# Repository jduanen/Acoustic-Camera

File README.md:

# Acoustic Camera — Project Summary

This project involves the design and implementation of a low-cost,
high-performance acoustic camera: i.e., a microphone array computes a power map
of the sound sources in a video camera's field of view and overlays it on the
video in real time.

Uses of such a device include locating vibration, gas leaks and electrical
breakdown, and as a hearing aid for people who can no longer localize sound
with one functional ear.

One of the top-level objectives for this project is to explore the use of
deep-learning models for this application and compare the performance and cost
with that of traditional DSP-based beamforming algorithms.

A full technical overview of the project can be found in [OVERVIEW.md](./OVERVIEW.md);
see the linked documents for more detail.

The Phase 3 prototype (4x4-mic array) unit looks like this:
<br>

This is an animation of the current state of the Phase 4 (96-mic spiral array) version's PCBs: 

See an example of a commercial product here [Fluke](https://youtu.be/UPVcwDzhBZ8) and a low-cost consumer product here [Fotric](https://youtu.be/MBhJoPzHv2Y)

## How it works

The microphone array samples the sound field at every mic at once. For each candidate direction
(azimuth, elevation), a **steering vector** describes the expected phase pattern across the
mics; a **beamformer** scores each direction against the measured **cross-spectral matrix
(CSM)** and the scores form the energy map overlaid on the video.

Three array properties set performance:

| Property | Controls | Rule |
|---|---|---|
| Aperture *D* | Beam width (resolution) and low-frequency limit | HPBW ≈ 58° × λ/*D*; useful directionality needs *f* > *c*/*D* |
| Minimum mic spacing *d* | High-frequency limit (grating lobes above it) | *f*<sub>Nyq</sub> = *c* / (2*d*) |
| Mic layout and count | Sidelobe level (MSL), SNR | Irregular spacing suppresses aliasing; more mics lower sidelobes |

Other key ideas: far field begins at *r* > 2*D*²/λ; the **point spread function** is how the
array smears a point source; commercial cameras average power incoherently across an octave
band to cut noise. Details: [BACKGROUND.md](./BACKGROUND.md), [MIC_ARRAYS.md](./MIC_ARRAYS.md).

**Algorithms explored** (one per family): Delay-and-Sum (simple, robust, wide beam), MVDR
(adaptive, suppresses interferers), CLEAN-SC (deconvolution, removes PSF artifacts), MUSIC
(subspace, super-resolution when the source count is known). ML methods come in Phase 5.

## Requirements and key design choices

| Parameter | Target |
|---|---|
| Frequency range | 200 Hz: 8 kHz (useful imaging from ~2 kHz) |
| Resolution (HPBW) | ~9.4° @ 8 kHz, ~19° @ 4 kHz, ~82° @ 1 kHz (simulated, Phase 4 array) |
| Distance | ~0.5 m (far-field limit) to ~10 m |
| Field of view | ±45° H, ±30° V, matched to the camera |
| Array | ~300 mm aperture, 96 MEMS mics, Underbrink 12 × 8 log-spiral, 12.94 mm min spacing (Nyquist ≈ 13.3 kHz) |

Why these numbers ([TRADEOFFS.md](./TRADEOFFS.md)):
- **300 mm aperture** is the practical sweet spot: portable, yet ~9° at 8 kHz. 5° at 1 kHz
  would need a ~4 m aperture.
- **96 mics** matches commercial practice (gfai Mikado uses 96 in the same pattern). Mic count
  grows as (aperture/spacing)², so going much smaller in spacing costs ~400+ mics.
- **Underbrink spiral** gave the best sidelobe suppression of all patterns simulated
  (−24.4 dB @ 4 kHz), with circular symmetry.
- **Beamforming grid**: 2–3 points per HPBW is enough. Finer grids cost memory and time
  (the steering matrix dominates) without improving resolution; the 96-mic array needs a
  finer grid than the UMA-16's 0.5°–1°.

## Development phases

Each phase delivers a working end-to-end system ([PLAN.md](./PLAN.md)).

| Phase | Hardware | Goal | Status |
|---|---|---|---|
| 1 | Simulation | Validate algorithms and array geometry | Complete |
| 2 | ReSpeaker XVF3800 (4 mics, 90 mm) | First end-to-end pipeline: capture → beamform → overlay | Complete |
| 3 | miniDSP UMA-16 v2 (16 mics, 126 mm) | 2D (az × el) beamforming, calibration, touch UI | Complete |
| 4 | Custom PCBs (96 mics, 300 mm, FPGA) | Full-performance system | In progress |
| 5 | Phase 3/4 hardware | ML beamformer (PILOT / CRNN) vs CLEAN-SC | Not started |

### Phase 1 — simulation ([PHASE1.md](./PHASE1.md))
- Recommended array: Underbrink 12 × 8, α = 22°, 96 mics, 300 mm, 12.9 mm minimum spacing, alias-free to ~13 kHz.
- HPBW: >180° below 500 Hz, ~82° @ 1 kHz, ~37° @ 2 kHz, ~19° @ 4 kHz, ~9° @ 8 kHz.
- Algorithm choice: CLEAN-SC for real-time single-source display; MVDR for multiple or weak
  sources; MUSIC for closely spaced sources with known count; D&S for lowest latency.
  256 snapshots per CSM.
- Works well: industrial source hunting at 2–8 kHz, multi-source scenes, normal rooms,
  near field at 0.5–3 m. Not suited: below 1 kHz, very reverberant spaces (DRR < 3 dB),
  separating sources on the same bearing, MUSIC at SNR < 10 dB.

### Phase 2 — ReSpeaker smoke test ([PHASE2.md](./PHASE2.md))
- Raw mics are USB channels 2–5; gain imbalance up to ~3.6× motivated calibration.
- D&S, MVDR and CLEAN-SC agreed within 5°. Live script: `src/acoustic_camera_p2.py`.

### Phase 3 — UMA-16 ([PHASE3.md](./PHASE3.md))
- 16 channels at 48 kHz, 2D beamforming with full-frame overlay on webcam or Pi camera.
- Live script `src/acoustic_camera_p3.py` with a touch UI: frequency sliders and spectrum
  pan, energy threshold (auto/manual), zoom/recenter/dwell, power indicator, saved settings.
- Shared math in `src/beamforming.py` (pytest suite in `tests/`); `src/benchmark_algos.py`
  measures per-algorithm cost. A 1°/pt grid brings all four algorithms within 20 fps.
- Lesson: the UMA-16's usable window is only ~2–4 kHz, bounded by aperture below and
  spatial Nyquist above.

### Phase 4 — custom hardware ([PHASE4.md](./PHASE4.md))
96-mic Underbrink spiral, 12 arms × 8 mics, with PDM → CIC/FIR decimation in an FPGA and
data streamed to a host (96 ch × 48 kHz × 24 bit ≈ 110 Mbit/s, within 1 GbE). A Pi Camera
Module 3 Wide mounts through the centre of the array.

- **Single-FPGA design (primary).** One ALINX AC7200 module (Xilinx XC7A200T) runs all 96
  channels plus a GbE/UDP link. RTL is done and fits (43.5% LUTs for the pipeline, 48.1% with
  the GbE MAC and packetizer). Two boards:
  - `mic_array`: Ø320 mm, 96 Infineon IM72D128 mics, TCXO and clock tree, local 3.3 V LDOs.
  - `front_end`: AC7200 module, power regulation, DP83867 GbE PHY.
  - Joined by Panasonic P5KS board-to-board connectors (9 mm mated height).
  - Status: the current Phase 4 design; PCBs being laid out and prepared for fabrication. See
    [pcb/SCHEMATIC_NOTES.md](./pcb/SCHEMATIC_NOTES.md) for the current schematic, power and
    connector details.
- **Multi-FPGA alternate.** Four Cmod A7-35T cluster boards (24 mics each) feed a hub board
  over a shared-clock spoke bus; the hub relays to a Raspberry Pi 5 over USB. Breadboarded
  and laid out as PCBs, but the boards were never built.

### Phase 5 — ML
Needs real Phase 3/4 data to train and validate models.

## Landscape

- **Commercial products** ([PRODUCTS.md](./PRODUCTS.md)): 64–96 MEMS mics is the sweet spot
  for handheld far-field use; USB for portable, PoE for fixed installs; a co-located video
  camera at the array centre is universal.
- **Open-source projects** ([PROJECTS.md](./PROJECTS.md)): FPGA → GbE → GPU host is the
  established pattern above ~96 mics; cross-correlation calibration with GPU gradient descent
  (Ben Wang) recovers mic positions and speed of sound. This project uses **Acoular** (Python)
  for parts of its beamforming work.

## Open questions and TODOs

- Match camera optics to the array's FOV and resolution
- Partition processing between FPGA and host; choose final processing/display hardware
- Packaging; low-noise audio front-end layout
- Add-on arms to extend the aperture for better low-frequency resolution

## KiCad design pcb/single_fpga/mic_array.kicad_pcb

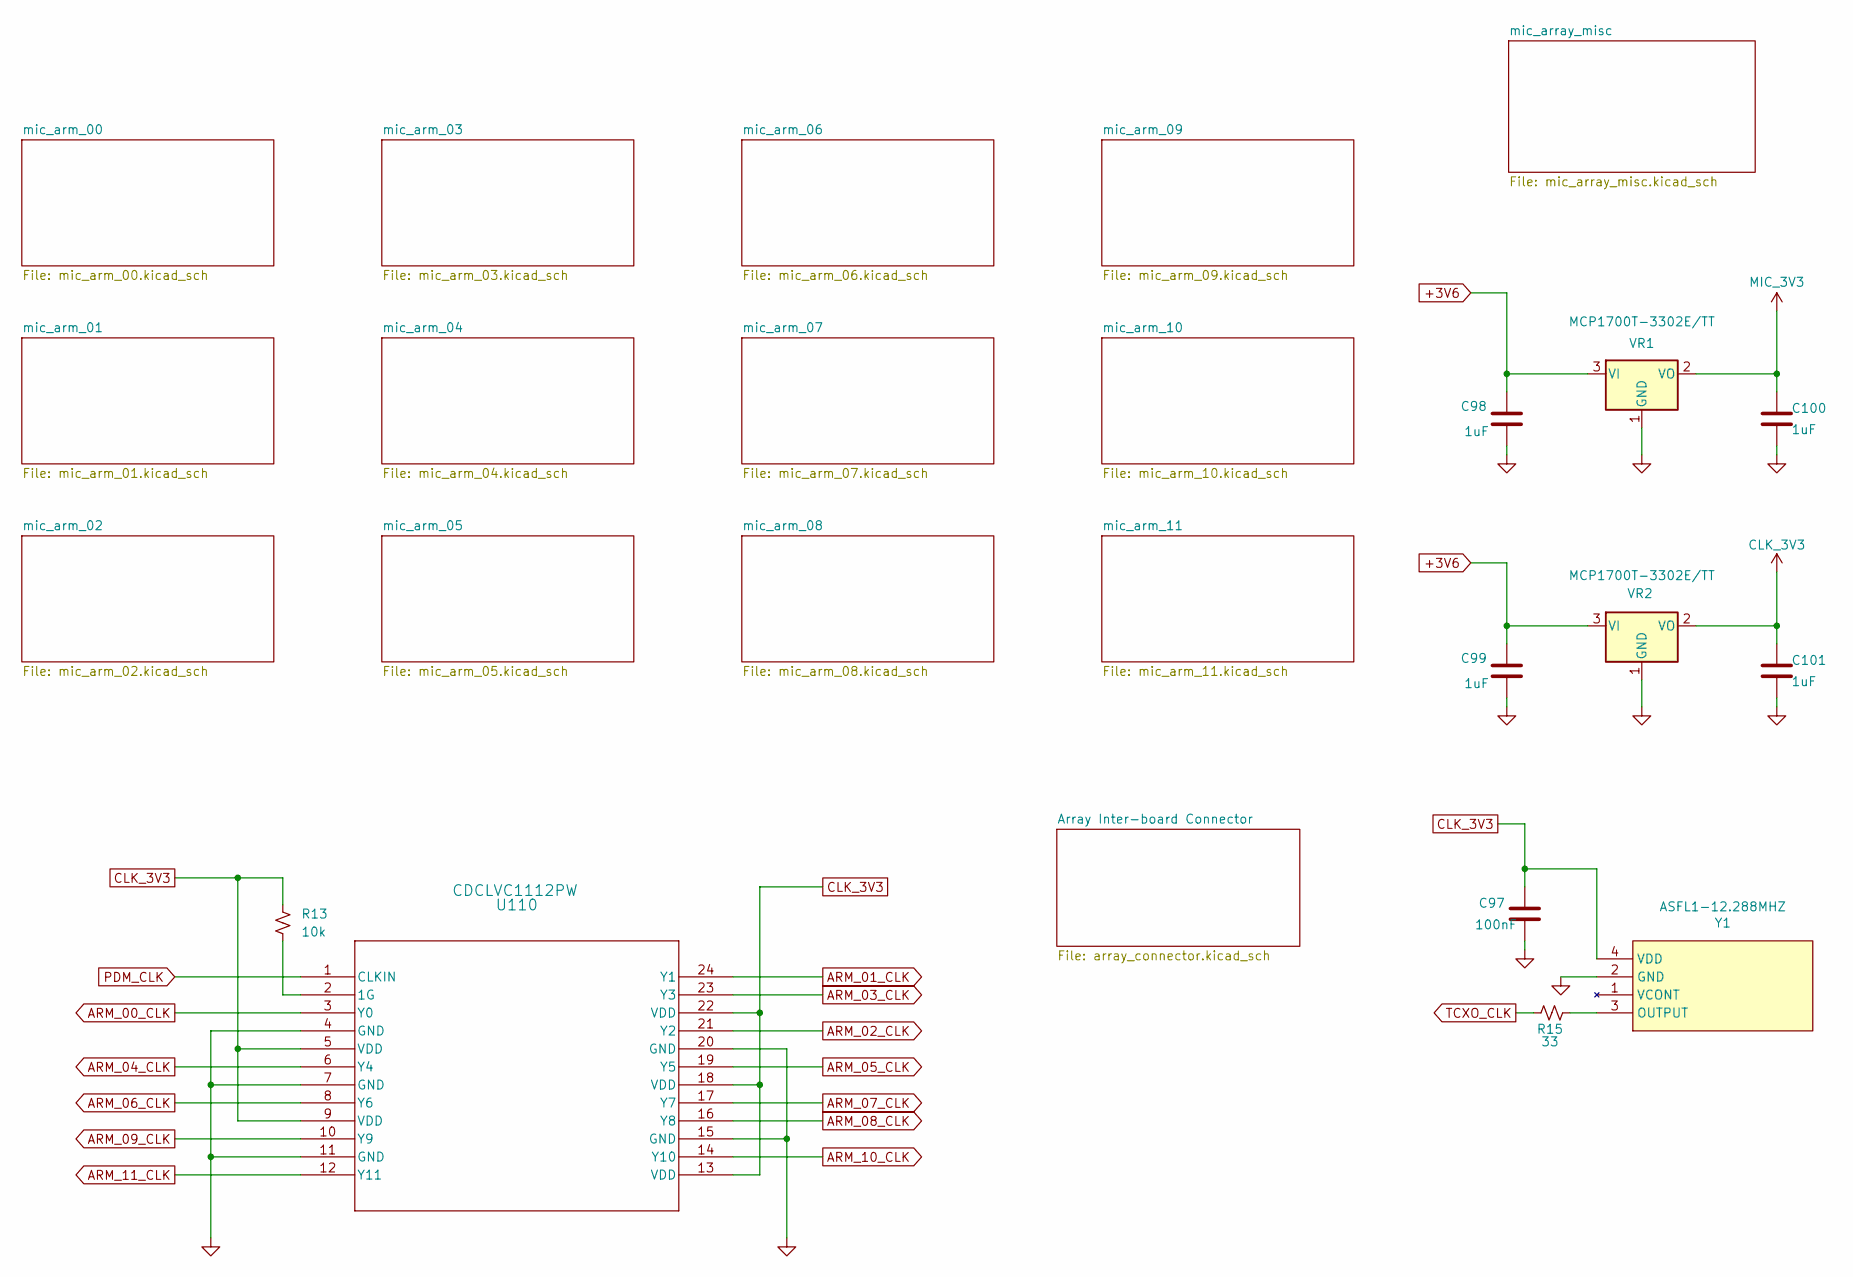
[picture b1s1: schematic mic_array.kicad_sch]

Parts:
C97: 100nF; C_0603_1608Metric; Part Number CC0603KRX7R9BB104; LCSC Part # C14663
C98, C99, C100, C101: 1uF; C_1206_3216Metric; Part Number CL31B105KBHNNNE; LCSC Part # C1848
R13: 10k; R_0603_1608Metric; Part Number 0603WAF1002T5E; LCSC Part # C25804
R15: 33; R_0603_1608Metric; Part Number 0603WAF330JT5E; LCSC Part # C23140
U110: CDCLVC1112PW; PW24; Part Number CDCLVC1112PWR; LCSC Part # C2876940
VR1, VR2: MCP1700T-3302E/TT; SOT-23; Part Number MCP1700T-3302E/TT; LCSC Part # C39051
Y1: ASFL1-12.288MHZ; Oscillator_SMD_SeikoEpson_SG8002LB-4Pin_5.0x3.2mm; Part Number ASFL1-12.288MHZ-LCS-T; LCSC Part # C276419

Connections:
+3V6: C98.1, C99.1, VR1.3 (VI), VR2.3 (VI); also elsewhere on the board
ARM_00_CLK: U110.3 (Y0); also elsewhere on the board
ARM_01_CLK: U110.24 (Y1); also elsewhere on the board
ARM_02_CLK: U110.21 (Y2); also elsewhere on the board
ARM_03_CLK: U110.23 (Y3); also elsewhere on the board
ARM_04_CLK: U110.6 (Y4); also elsewhere on the board
ARM_05_CLK: U110.19 (Y5); also elsewhere on the board
ARM_06_CLK: U110.8 (Y6); also elsewhere on the board
ARM_07_CLK: U110.17 (Y7); also elsewhere on the board
ARM_08_CLK: U110.16 (Y8); also elsewhere on the board
ARM_09_CLK: U110.10 (Y9); also elsewhere on the board
ARM_10_CLK: U110.14 (Y10); also elsewhere on the board
ARM_11_CLK: U110.12 (Y11); also elsewhere on the board
CLK_3V3: C97.1, C101.1, R13.2, U110.5 (VDD), U110.9 (VDD), U110.13 (VDD), U110.18 (VDD), U110.22 (VDD), VR2.2 (VO), Y1.4 (VDD); also elsewhere on the board
GND: C97.2, C98.2, C99.2, C100.2, C101.2, U110.4 (GND), U110.7 (GND), U110.11 (GND), U110.15 (GND), U110.20 (GND), VR1.1 (GND), VR2.1 (GND), Y1.2 (GND); also elsewhere on the board
MIC_3V3: C100.1, VR1.2 (VO); also elsewhere on the board
unnamed: R13.1, U110.2 (1G)
unnamed: R15.2, Y1.3 (OUTPUT)
PDM_CLK: U110.1 (CLKIN); also elsewhere on the board
TCXO_CLK: R15.1; also elsewhere on the board

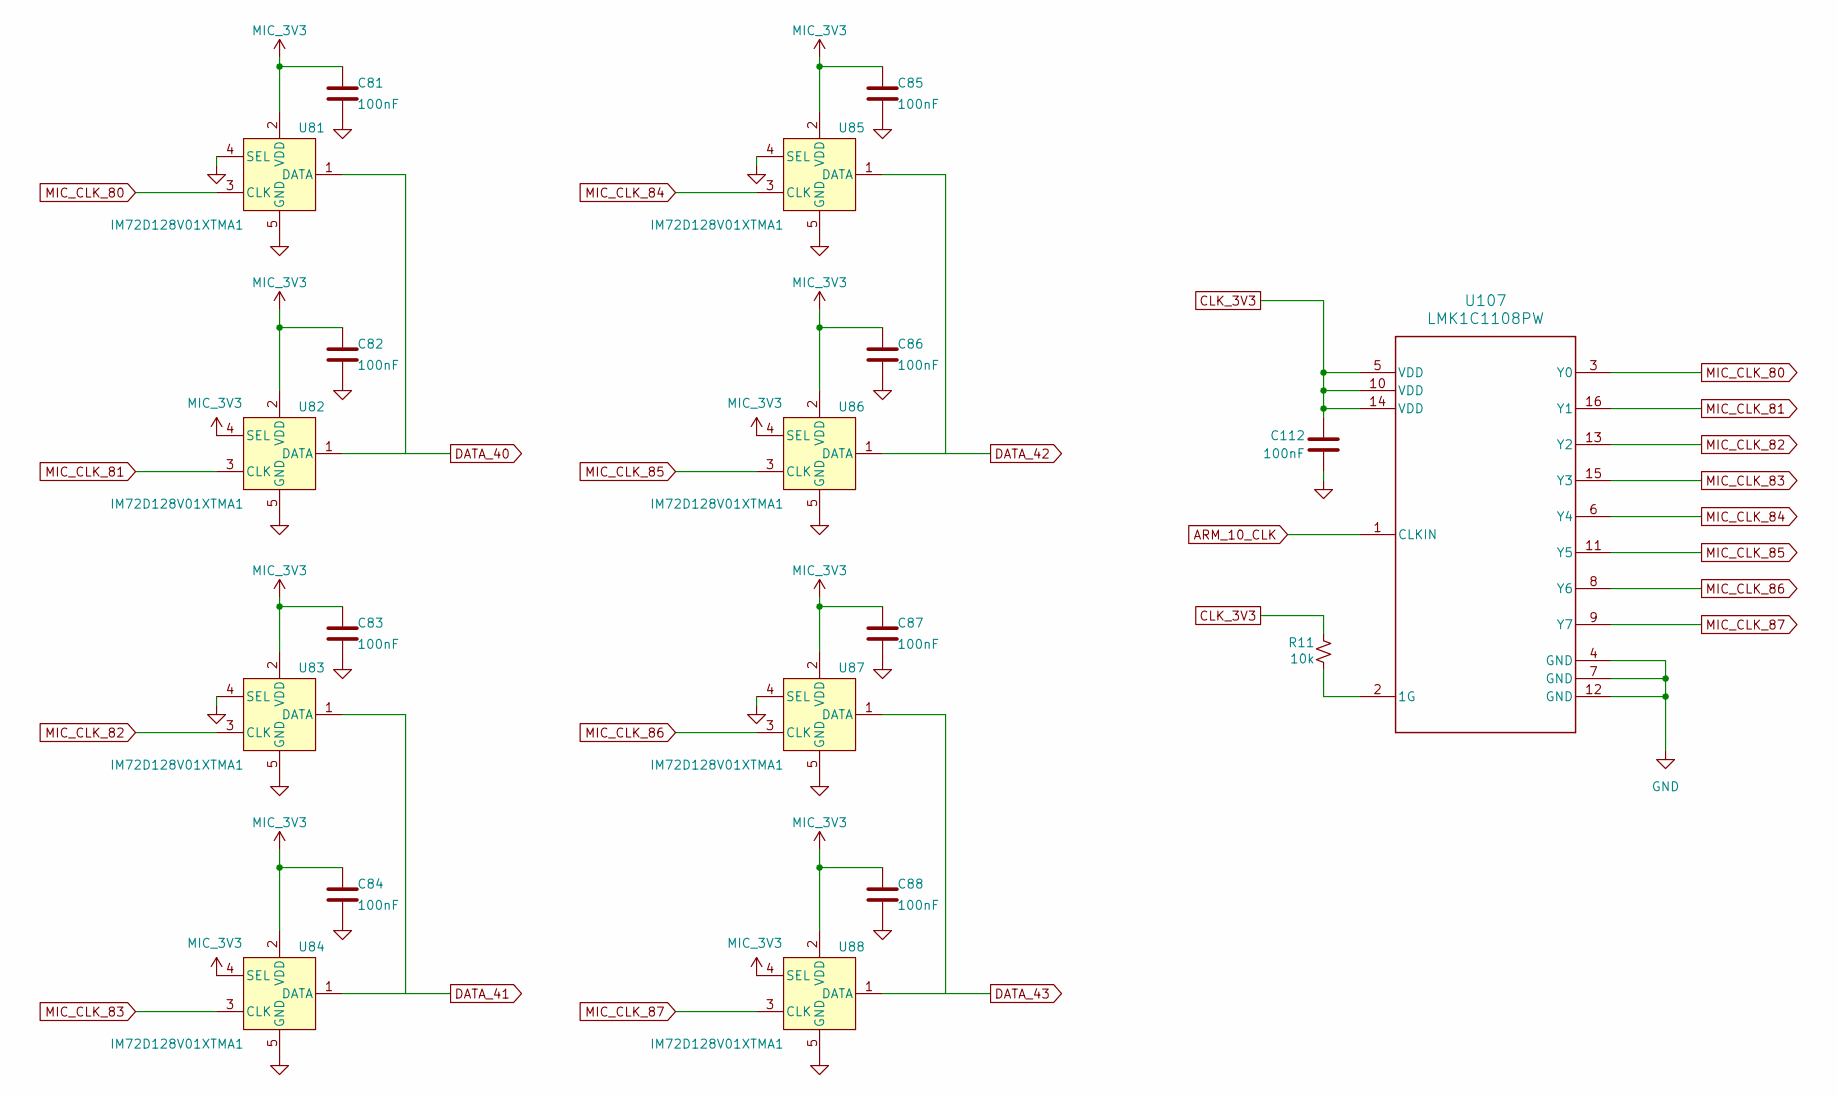
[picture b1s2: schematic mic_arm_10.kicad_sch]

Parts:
C81, C82, C83, C84, C85, C86, C87, C88, C112: 100nF; C_0603_1608Metric; Part Number CC0603KRX7R9BB104; LCSC Part # C14663
R11: 10k; R_0603_1608Metric; Part Number 0603WAF1002T5E; LCSC Part # C25804
U81, U82, U83, U84, U85, U86, U87, U88: IM72D128V01XTMA1; IFX-PG-LLGA-5-4; Part Number IM72D128V01XTMA1; LCSC Part # C5119248
U107: LMK1C1108PW; PW0016A_N; Part Number LMK1C1108PWR; LCSC Part # C2868241

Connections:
ARM_10_CLK: U107.1 (CLKIN); also elsewhere on the board
CLK_3V3: C112.2, R11.2, U107.5 (VDD), U107.10 (VDD), U107.14 (VDD); also elsewhere on the board
DATA_40: U81.1 (DATA), U82.1 (DATA); also elsewhere on the board
DATA_41: U83.1 (DATA), U84.1 (DATA); also elsewhere on the board
DATA_42: U85.1 (DATA), U86.1 (DATA); also elsewhere on the board
DATA_43: U87.1 (DATA), U88.1 (DATA); also elsewhere on the board
GND: C81.2, C82.2, C83.2, C84.2, C85.2, C86.2, C87.2, C88.2, C112.1, U81.4 (SEL), U81.5 (GND), U82.5 (GND), U83.4 (SEL), U83.5 (GND), U84.5 (GND), U85.4 (SEL), U85.5 (GND), U86.5 (GND), U87.4 (SEL), U87.5 (GND), U88.5 (GND), U107.4 (GND), U107.7 (GND), U107.12 (GND); also elsewhere on the board
MIC_3V3: C81.1, C82.1, C83.1, C84.1, C85.1, C86.1, C87.1, C88.1, U81.2 (VDD), U82.2 (VDD), U82.4 (SEL), U83.2 (VDD), U84.2 (VDD), U84.4 (SEL), U85.2 (VDD), U86.2 (VDD), U86.4 (SEL), U87.2 (VDD), U88.2 (VDD), U88.4 (SEL); also elsewhere on the board
MIC_CLK_80: U81.3 (CLK), U107.3 (Y0)
MIC_CLK_81: U82.3 (CLK), U107.16 (Y1)
MIC_CLK_82: U83.3 (CLK), U107.13 (Y2)
MIC_CLK_83: U84.3 (CLK), U107.15 (Y3)
MIC_CLK_84: U85.3 (CLK), U107.6 (Y4)
MIC_CLK_85: U86.3 (CLK), U107.11 (Y5)
MIC_CLK_86: U87.3 (CLK), U107.8 (Y6)
MIC_CLK_87: U88.3 (CLK), U107.9 (Y7)
unnamed: R11.1, U107.2 (1G)

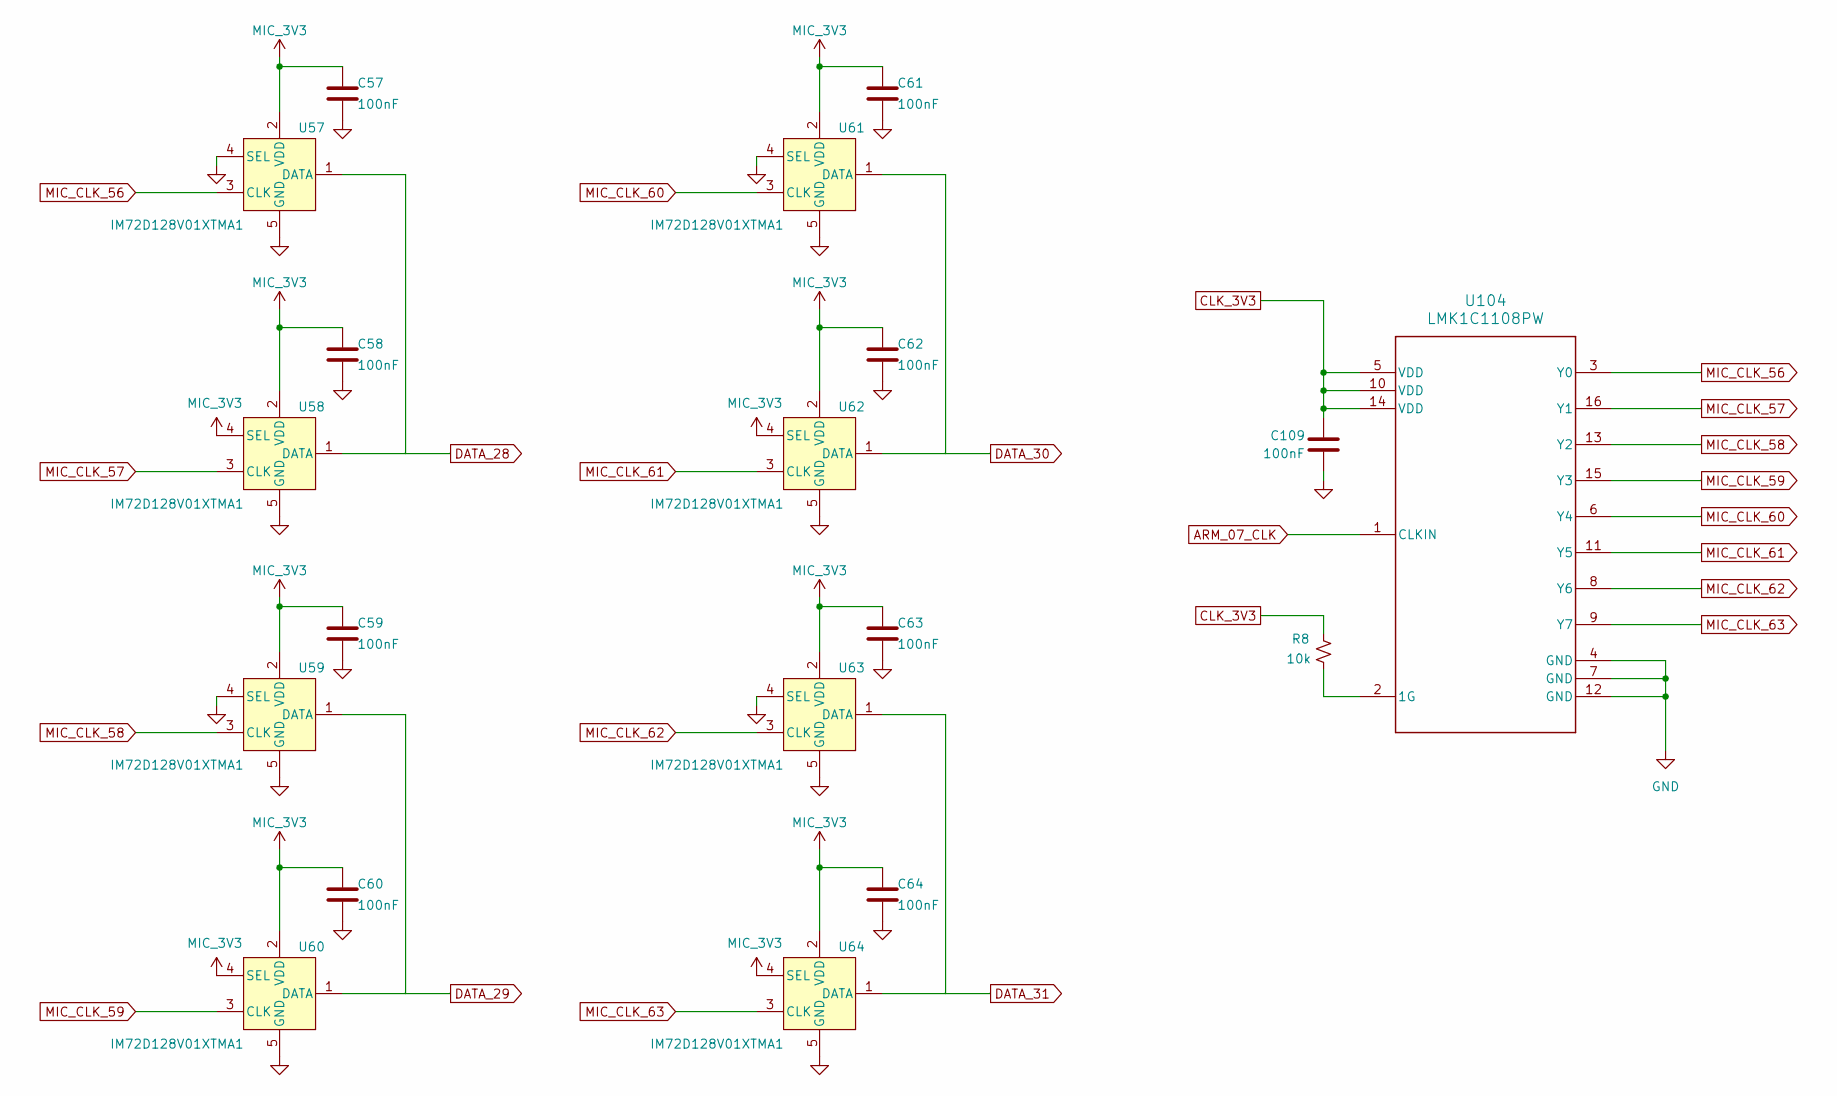
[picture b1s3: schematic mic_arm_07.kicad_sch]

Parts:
C57, C58, C59, C60, C61, C62, C63, C64, C109: 100nF; C_0603_1608Metric; Part Number CC0603KRX7R9BB104; LCSC Part # C14663
R8: 10k; R_0603_1608Metric; Part Number 0603WAF1002T5E; LCSC Part # C25804
U57, U58, U59, U60, U61, U62, U63, U64: IM72D128V01XTMA1; IFX-PG-LLGA-5-4; Part Number IM72D128V01XTMA1; LCSC Part # C5119248
U104: LMK1C1108PW; PW0016A_N; Part Number LMK1C1108PWR; LCSC Part # C2868241

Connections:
ARM_07_CLK: U104.1 (CLKIN); also elsewhere on the board
CLK_3V3: C109.2, R8.2, U104.5 (VDD), U104.10 (VDD), U104.14 (VDD); also elsewhere on the board
DATA_28: U57.1 (DATA), U58.1 (DATA); also elsewhere on the board
DATA_29: U59.1 (DATA), U60.1 (DATA); also elsewhere on the board
DATA_30: U61.1 (DATA), U62.1 (DATA); also elsewhere on the board
DATA_31: U63.1 (DATA), U64.1 (DATA); also elsewhere on the board
GND: C57.2, C58.2, C59.2, C60.2, C61.2, C62.2, C63.2, C64.2, C109.1, U57.4 (SEL), U57.5 (GND), U58.5 (GND), U59.4 (SEL), U59.5 (GND), U60.5 (GND), U61.4 (SEL), U61.5 (GND), U62.5 (GND), U63.4 (SEL), U63.5 (GND), U64.5 (GND), U104.4 (GND), U104.7 (GND), U104.12 (GND); also elsewhere on the board
MIC_3V3: C57.1, C58.1, C59.1, C60.1, C61.1, C62.1, C63.1, C64.1, U57.2 (VDD), U58.2 (VDD), U58.4 (SEL), U59.2 (VDD), U60.2 (VDD), U60.4 (SEL), U61.2 (VDD), U62.2 (VDD), U62.4 (SEL), U63.2 (VDD), U64.2 (VDD), U64.4 (SEL); also elsewhere on the board
MIC_CLK_56: U57.3 (CLK), U104.3 (Y0)
MIC_CLK_57: U58.3 (CLK), U104.16 (Y1)
MIC_CLK_58: U59.3 (CLK), U104.13 (Y2)
MIC_CLK_59: U60.3 (CLK), U104.15 (Y3)
MIC_CLK_60: U61.3 (CLK), U104.6 (Y4)
MIC_CLK_61: U62.3 (CLK), U104.11 (Y5)
MIC_CLK_62: U63.3 (CLK), U104.8 (Y6)
MIC_CLK_63: U64.3 (CLK), U104.9 (Y7)
unnamed: R8.1, U104.2 (1G)

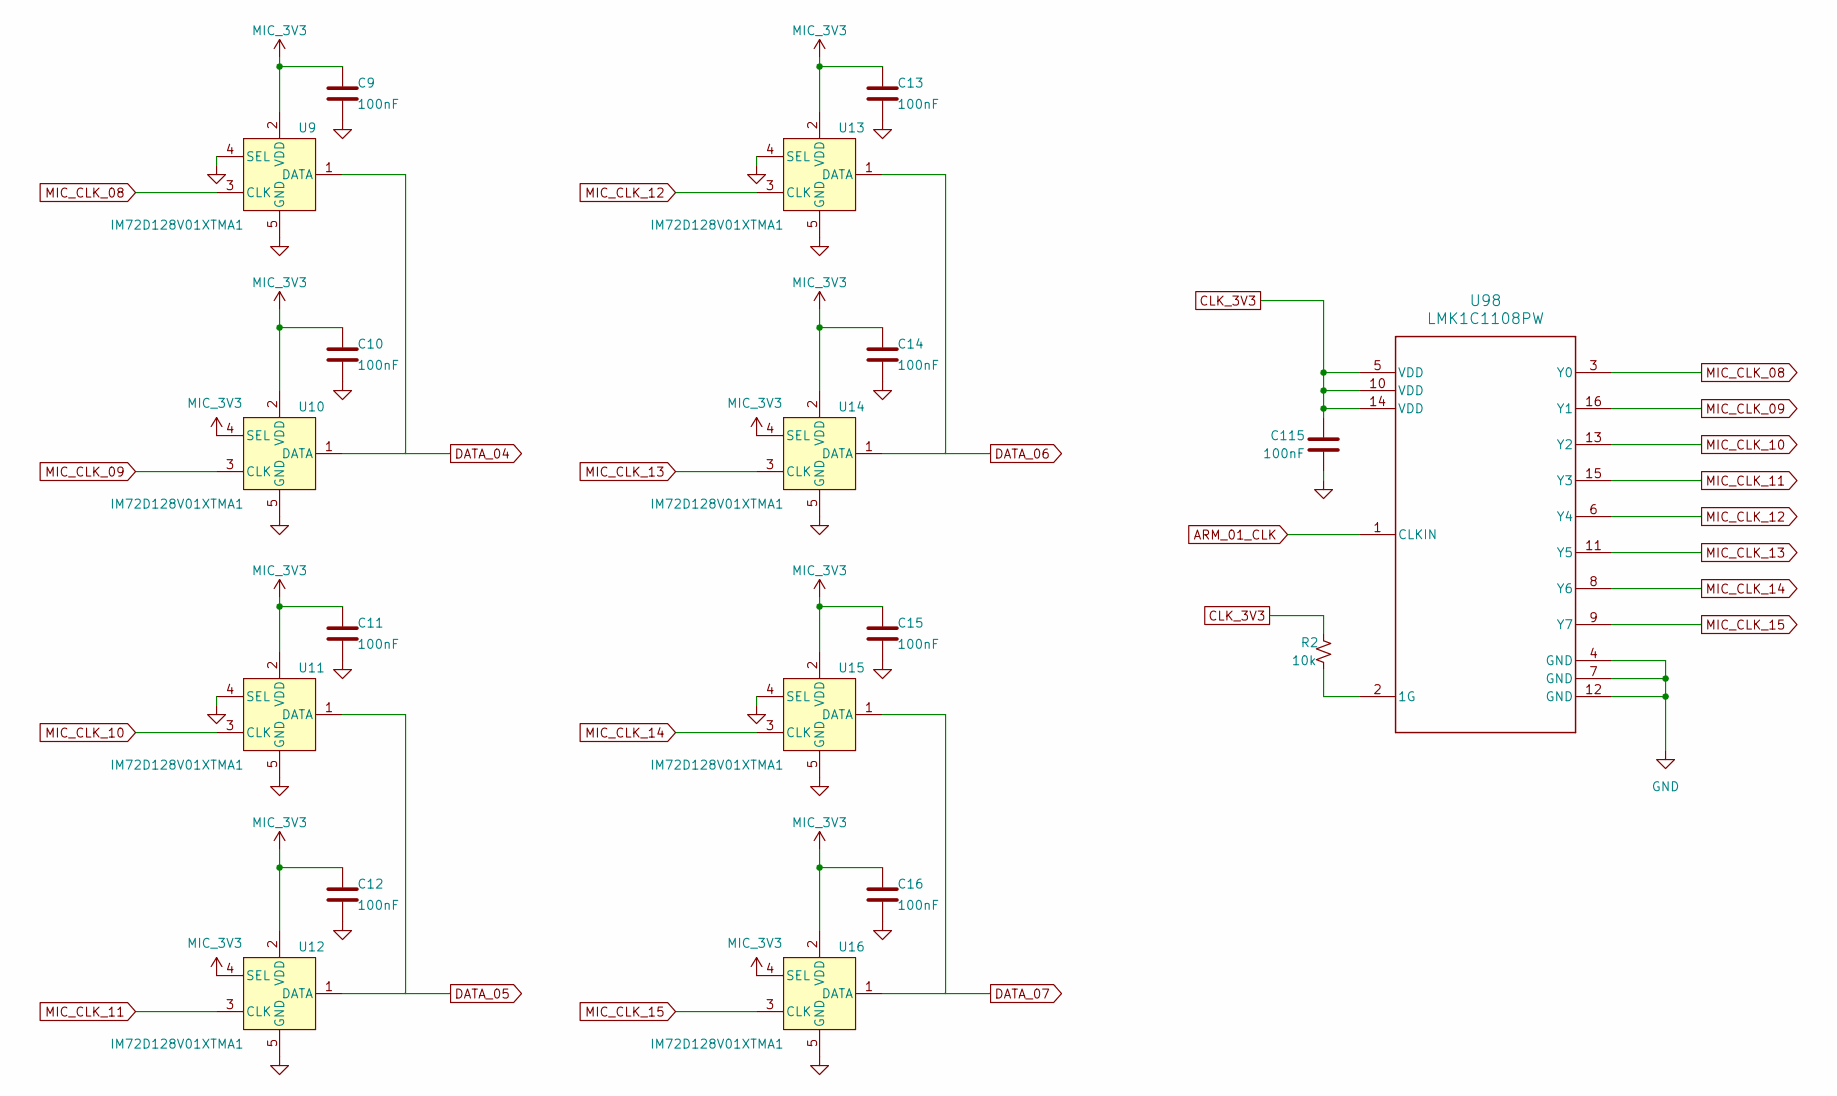
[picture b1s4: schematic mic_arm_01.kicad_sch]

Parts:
C9, C10, C11, C12, C13, C14, C15, C16, C115: 100nF; C_0603_1608Metric; Part Number CC0603KRX7R9BB104; LCSC Part # C14663
R2: 10k; R_0603_1608Metric; Part Number 0603WAF1002T5E; LCSC Part # C25804
U9, U10, U11, U12, U13, U14, U15, U16: IM72D128V01XTMA1; IFX-PG-LLGA-5-4; Part Number IM72D128V01XTMA1; LCSC Part # C5119248
U98: LMK1C1108PW; PW0016A_N; Part Number LMK1C1108PWR; LCSC Part # C2868241

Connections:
ARM_01_CLK: U98.1 (CLKIN); also elsewhere on the board
CLK_3V3: C115.1, R2.2, U98.5 (VDD), U98.10 (VDD), U98.14 (VDD); also elsewhere on the board
DATA_04: U9.1 (DATA), U10.1 (DATA); also elsewhere on the board
DATA_05: U11.1 (DATA), U12.1 (DATA); also elsewhere on the board
DATA_06: U13.1 (DATA), U14.1 (DATA); also elsewhere on the board
DATA_07: U15.1 (DATA), U16.1 (DATA); also elsewhere on the board
GND: C9.2, C10.2, C11.2, C12.2, C13.2, C14.2, C15.2, C16.2, C115.2, U9.4 (SEL), U9.5 (GND), U10.5 (GND), U11.4 (SEL), U11.5 (GND), U12.5 (GND), U13.4 (SEL), U13.5 (GND), U14.5 (GND), U15.4 (SEL), U15.5 (GND), U16.5 (GND), U98.4 (GND), U98.7 (GND), U98.12 (GND); also elsewhere on the board
MIC_3V3: C9.1, C10.1, C11.1, C12.1, C13.1, C14.1, C15.1, C16.1, U9.2 (VDD), U10.2 (VDD), U10.4 (SEL), U11.2 (VDD), U12.2 (VDD), U12.4 (SEL), U13.2 (VDD), U14.2 (VDD), U14.4 (SEL), U15.2 (VDD), U16.2 (VDD), U16.4 (SEL); also elsewhere on the board
MIC_CLK_08: U9.3 (CLK), U98.3 (Y0)
MIC_CLK_09: U10.3 (CLK), U98.16 (Y1)
MIC_CLK_10: U11.3 (CLK), U98.13 (Y2)
MIC_CLK_11: U12.3 (CLK), U98.15 (Y3)
MIC_CLK_12: U13.3 (CLK), U98.6 (Y4)
MIC_CLK_13: U14.3 (CLK), U98.11 (Y5)
MIC_CLK_14: U15.3 (CLK), U98.8 (Y6)
MIC_CLK_15: U16.3 (CLK), U98.9 (Y7)
unnamed: R2.1, U98.2 (1G)

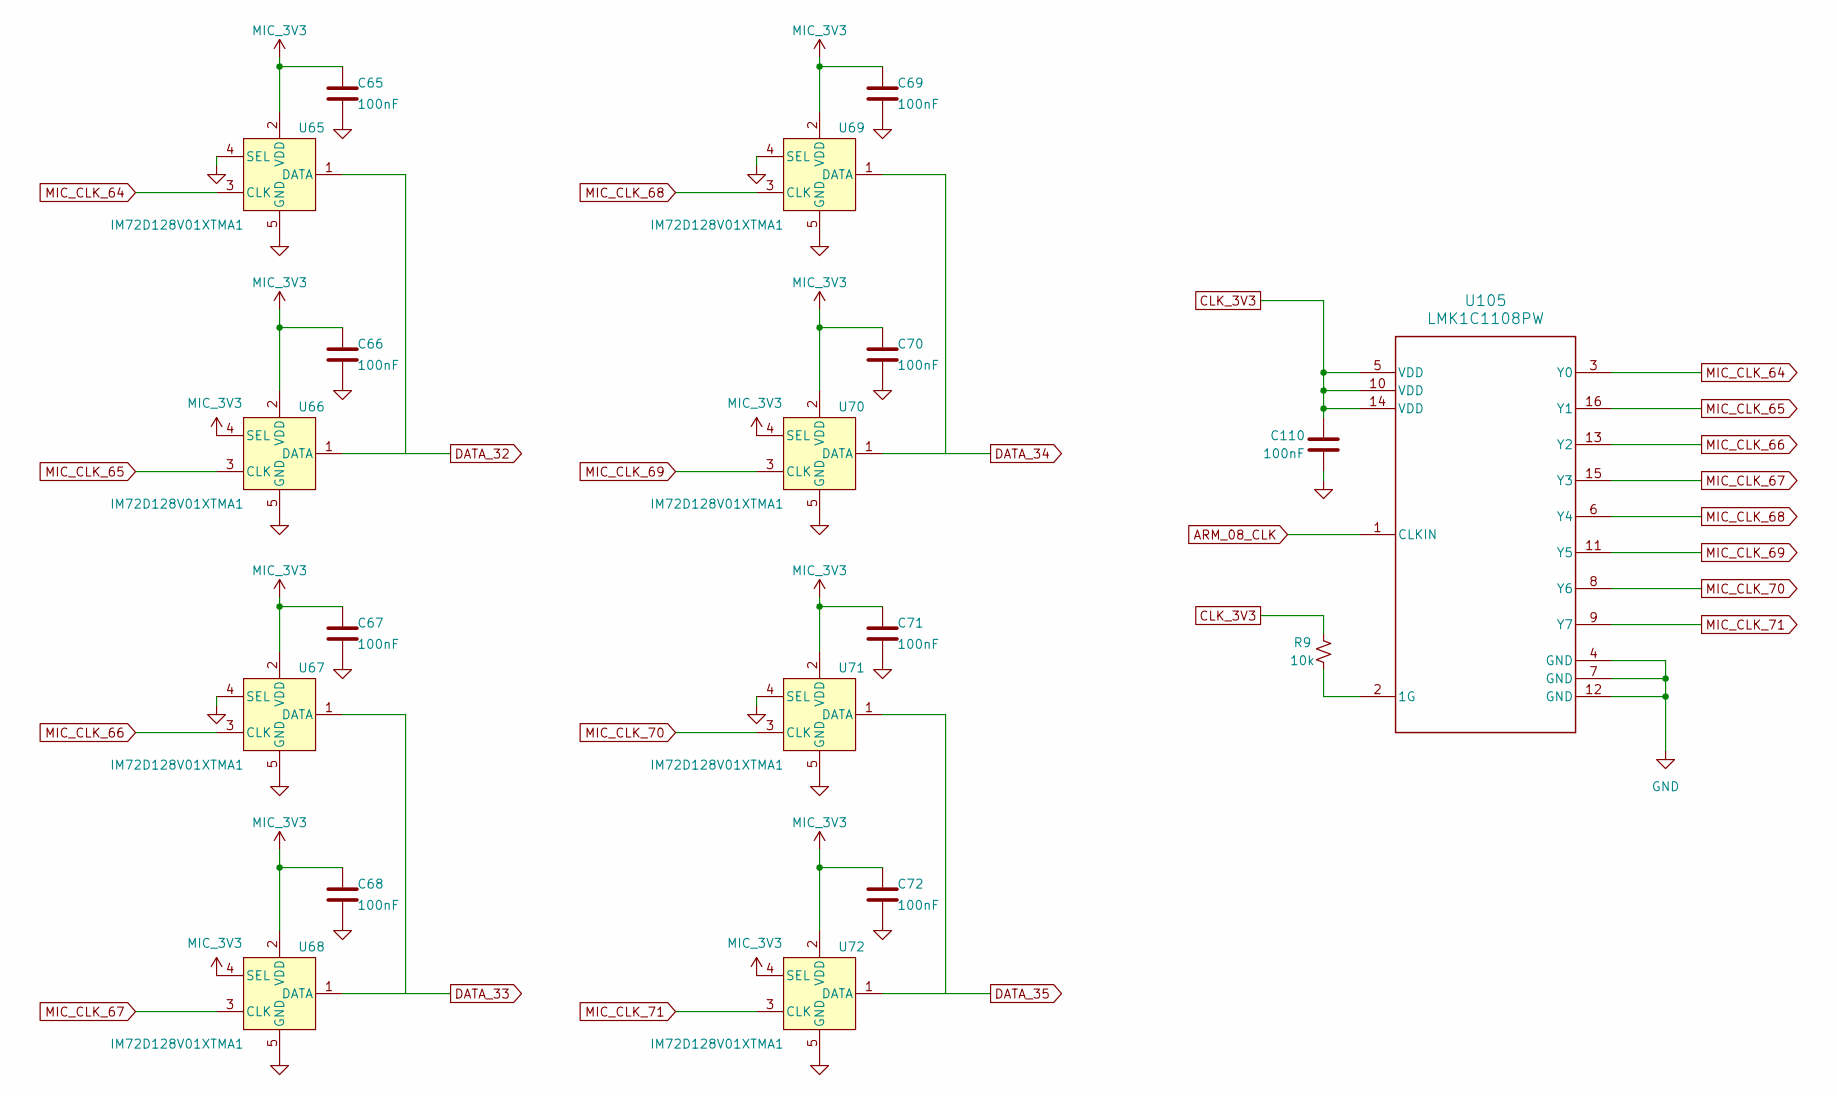
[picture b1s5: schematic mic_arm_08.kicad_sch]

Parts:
C65, C66, C67, C68, C69, C70, C71, C72, C110: 100nF; C_0603_1608Metric; Part Number CC0603KRX7R9BB104; LCSC Part # C14663
R9: 10k; R_0603_1608Metric; Part Number 0603WAF1002T5E; LCSC Part # C25804
U65, U66, U67, U68, U69, U70, U71, U72: IM72D128V01XTMA1; IFX-PG-LLGA-5-4; Part Number IM72D128V01XTMA1; LCSC Part # C5119248
U105: LMK1C1108PW; PW0016A_N; Part Number LMK1C1108PWR; LCSC Part # C2868241

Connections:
ARM_08_CLK: U105.1 (CLKIN); also elsewhere on the board
CLK_3V3: C110.2, R9.2, U105.5 (VDD), U105.10 (VDD), U105.14 (VDD); also elsewhere on the board
DATA_32: U65.1 (DATA), U66.1 (DATA); also elsewhere on the board
DATA_33: U67.1 (DATA), U68.1 (DATA); also elsewhere on the board
DATA_34: U69.1 (DATA), U70.1 (DATA); also elsewhere on the board
DATA_35: U71.1 (DATA), U72.1 (DATA); also elsewhere on the board
GND: C65.2, C66.2, C67.2, C68.2, C69.2, C70.2, C71.2, C72.2, C110.1, U65.4 (SEL), U65.5 (GND), U66.5 (GND), U67.4 (SEL), U67.5 (GND), U68.5 (GND), U69.4 (SEL), U69.5 (GND), U70.5 (GND), U71.4 (SEL), U71.5 (GND), U72.5 (GND), U105.4 (GND), U105.7 (GND), U105.12 (GND); also elsewhere on the board
MIC_3V3: C65.1, C66.1, C67.1, C68.1, C69.1, C70.1, C71.1, C72.1, U65.2 (VDD), U66.2 (VDD), U66.4 (SEL), U67.2 (VDD), U68.2 (VDD), U68.4 (SEL), U69.2 (VDD), U70.2 (VDD), U70.4 (SEL), U71.2 (VDD), U72.2 (VDD), U72.4 (SEL); also elsewhere on the board
MIC_CLK_64: U65.3 (CLK), U105.3 (Y0)
MIC_CLK_65: U66.3 (CLK), U105.16 (Y1)
MIC_CLK_66: U67.3 (CLK), U105.13 (Y2)
MIC_CLK_67: U68.3 (CLK), U105.15 (Y3)
MIC_CLK_68: U69.3 (CLK), U105.6 (Y4)
MIC_CLK_69: U70.3 (CLK), U105.11 (Y5)
MIC_CLK_70: U71.3 (CLK), U105.8 (Y6)
MIC_CLK_71: U72.3 (CLK), U105.9 (Y7)
unnamed: R9.1, U105.2 (1G)

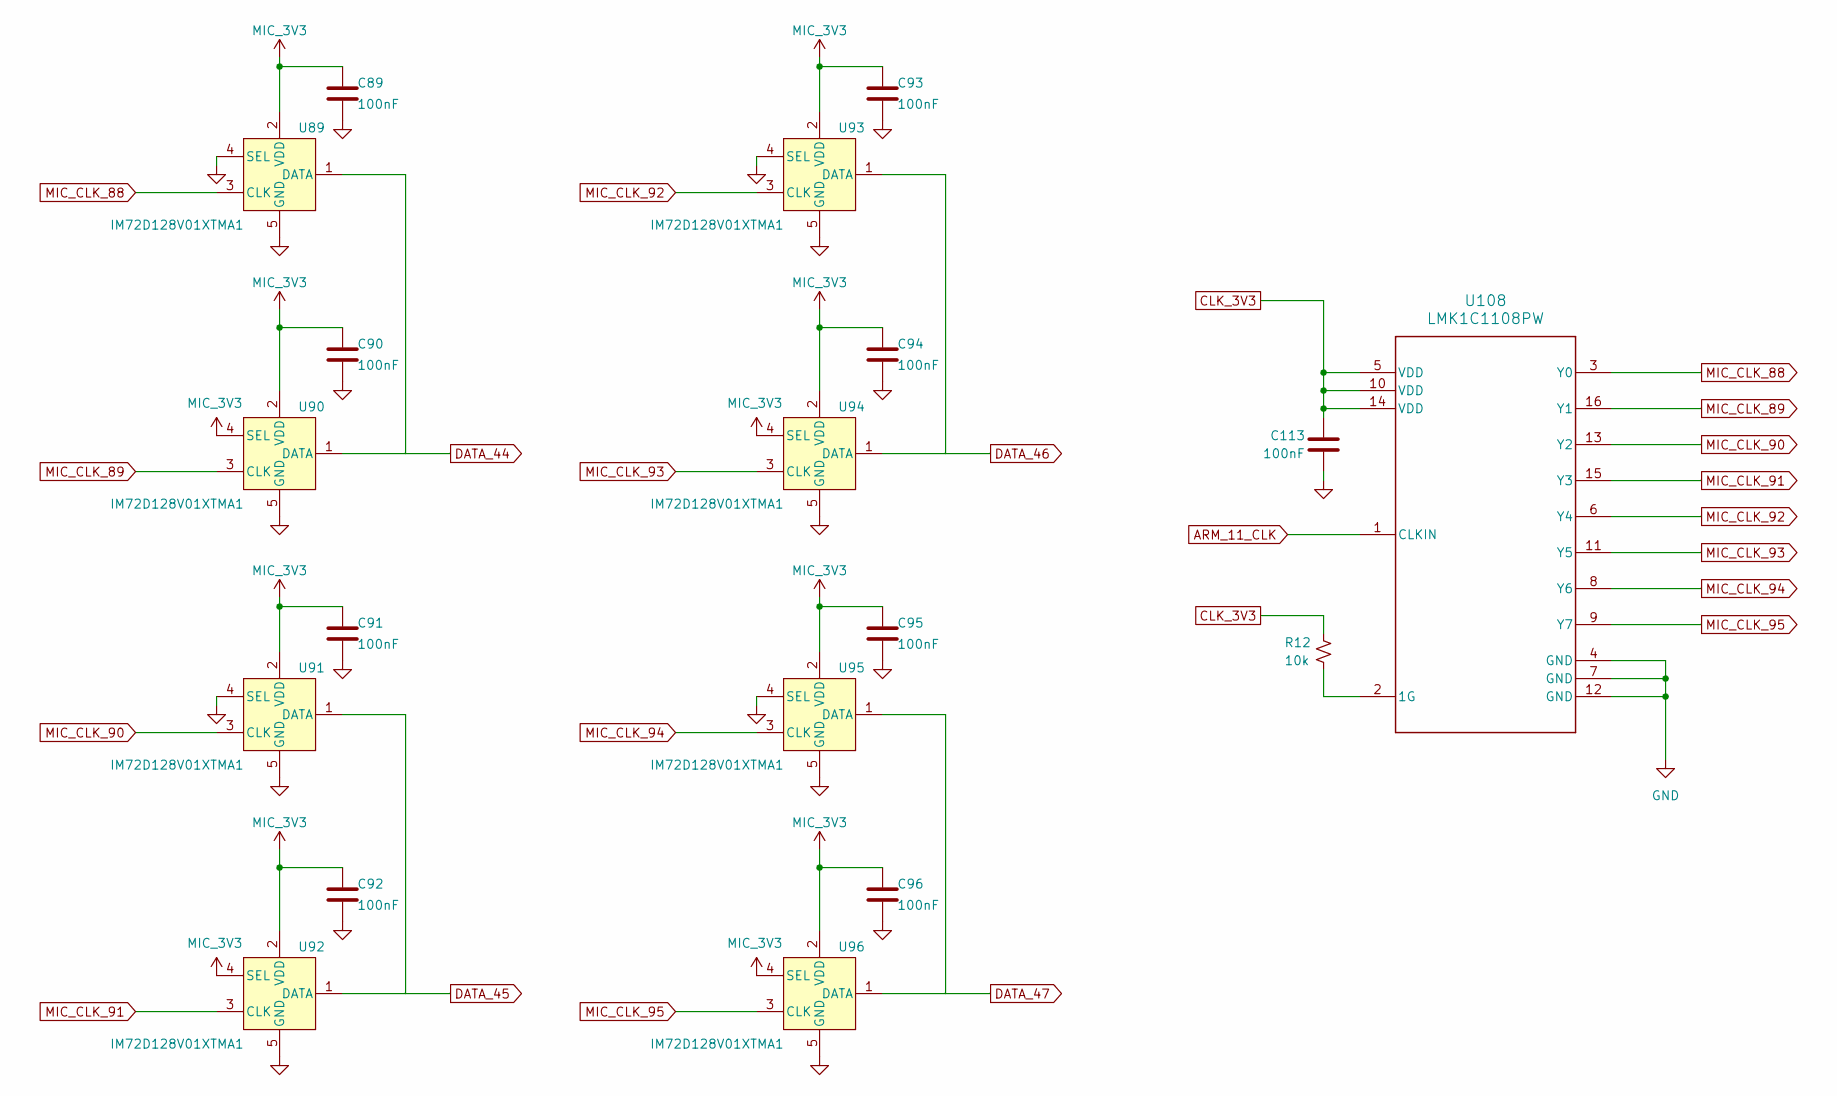
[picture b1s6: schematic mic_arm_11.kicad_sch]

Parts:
C89, C90, C91, C92, C93, C94, C95, C96, C113: 100nF; C_0603_1608Metric; Part Number CC0603KRX7R9BB104; LCSC Part # C14663
R12: 10k; R_0603_1608Metric; Part Number 0603WAF1002T5E; LCSC Part # C25804
U89, U90, U91, U92, U93, U94, U95, U96: IM72D128V01XTMA1; IFX-PG-LLGA-5-4; Part Number IM72D128V01XTMA1; LCSC Part # C5119248
U108: LMK1C1108PW; PW0016A_N; Part Number LMK1C1108PWR; LCSC Part # C2868241

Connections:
ARM_11_CLK: U108.1 (CLKIN); also elsewhere on the board
CLK_3V3: C113.2, R12.2, U108.5 (VDD), U108.10 (VDD), U108.14 (VDD); also elsewhere on the board
DATA_44: U89.1 (DATA), U90.1 (DATA); also elsewhere on the board
DATA_45: U91.1 (DATA), U92.1 (DATA); also elsewhere on the board
DATA_46: U93.1 (DATA), U94.1 (DATA); also elsewhere on the board
DATA_47: U95.1 (DATA), U96.1 (DATA); also elsewhere on the board
GND: C89.2, C90.2, C91.2, C92.2, C93.2, C94.2, C95.2, C96.2, C113.1, U89.4 (SEL), U89.5 (GND), U90.5 (GND), U91.4 (SEL), U91.5 (GND), U92.5 (GND), U93.4 (SEL), U93.5 (GND), U94.5 (GND), U95.4 (SEL), U95.5 (GND), U96.5 (GND), U108.4 (GND), U108.7 (GND), U108.12 (GND); also elsewhere on the board
MIC_3V3: C89.1, C90.1, C91.1, C92.1, C93.1, C94.1, C95.1, C96.1, U89.2 (VDD), U90.2 (VDD), U90.4 (SEL), U91.2 (VDD), U92.2 (VDD), U92.4 (SEL), U93.2 (VDD), U94.2 (VDD), U94.4 (SEL), U95.2 (VDD), U96.2 (VDD), U96.4 (SEL); also elsewhere on the board
MIC_CLK_88: U89.3 (CLK), U108.3 (Y0)
MIC_CLK_89: U90.3 (CLK), U108.16 (Y1)
MIC_CLK_90: U91.3 (CLK), U108.13 (Y2)
MIC_CLK_91: U92.3 (CLK), U108.15 (Y3)
MIC_CLK_92: U93.3 (CLK), U108.6 (Y4)
MIC_CLK_93: U94.3 (CLK), U108.11 (Y5)
MIC_CLK_94: U95.3 (CLK), U108.8 (Y6)
MIC_CLK_95: U96.3 (CLK), U108.9 (Y7)
unnamed: R12.1, U108.2 (1G)
